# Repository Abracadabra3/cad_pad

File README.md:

# CAD Pad
**A macropad with Autodesk Fusion shortcuts, a numberpad, and general shortcuts.**

## Features
- Layer 0: A numberpad
- Layer 1: Shortcuts for Autodesk Fusion
- Layer 2: General shortcuts for outside of Fusion
- Layer 3: Shorcuts for inside a Fusion sketch
- A shortcut for opening the parameter dialogue
- A made-from-scratch 7-segment display!

## BOM
- 1 unsoldered Seeed XIAO RP2040
- 12 through-hole 1N4148 diodes
- 12 MX-Style switches
- 12 DSA keycaps
- 7 SK6812 MINI-E LEDs
- 4 M3x16mm screws
- 4 M3x5x4mm heatset inserts
- 2 7 pin headers
- 0.91 inch OLED display (Optional)
- 4 pin header (Only if OLED display used)
- EC11 Rotary encoders (Optional)

## Design decisions
I chose the 12 key layout of the CAD Pad to mimic a numberpad and still have extra pins on the Seeeduino. The PCB has a connector for both a rotary encode and an OLED display. Neither are in the firmware right now and there is only enough pins for one at a time, but both are options for the future.
I didn't feel like figuring out how to use the OLED display, so instead I made a 7-segment display with LEDs and coded it to display the layer number!

## References
I followed many tutorials other than the [Stardance guide](https://hackpad.hackclub.com/guide) to making a macropad.
- [Creating a matrix in KiCad](youtube.com/watch?v=8WXpGTIbxlQ)
- [Setting up QMK](youtube.com/watch?v=hjml-K-pV4E)
- [Layers in QMK](keebsforall.com/blogs/mechanical-keyboards-101/how-to-add-layers-in-qmk)
- [Macros in QMK](getreuer.info/posts/keyboards/macros/index.html#simple-macros)

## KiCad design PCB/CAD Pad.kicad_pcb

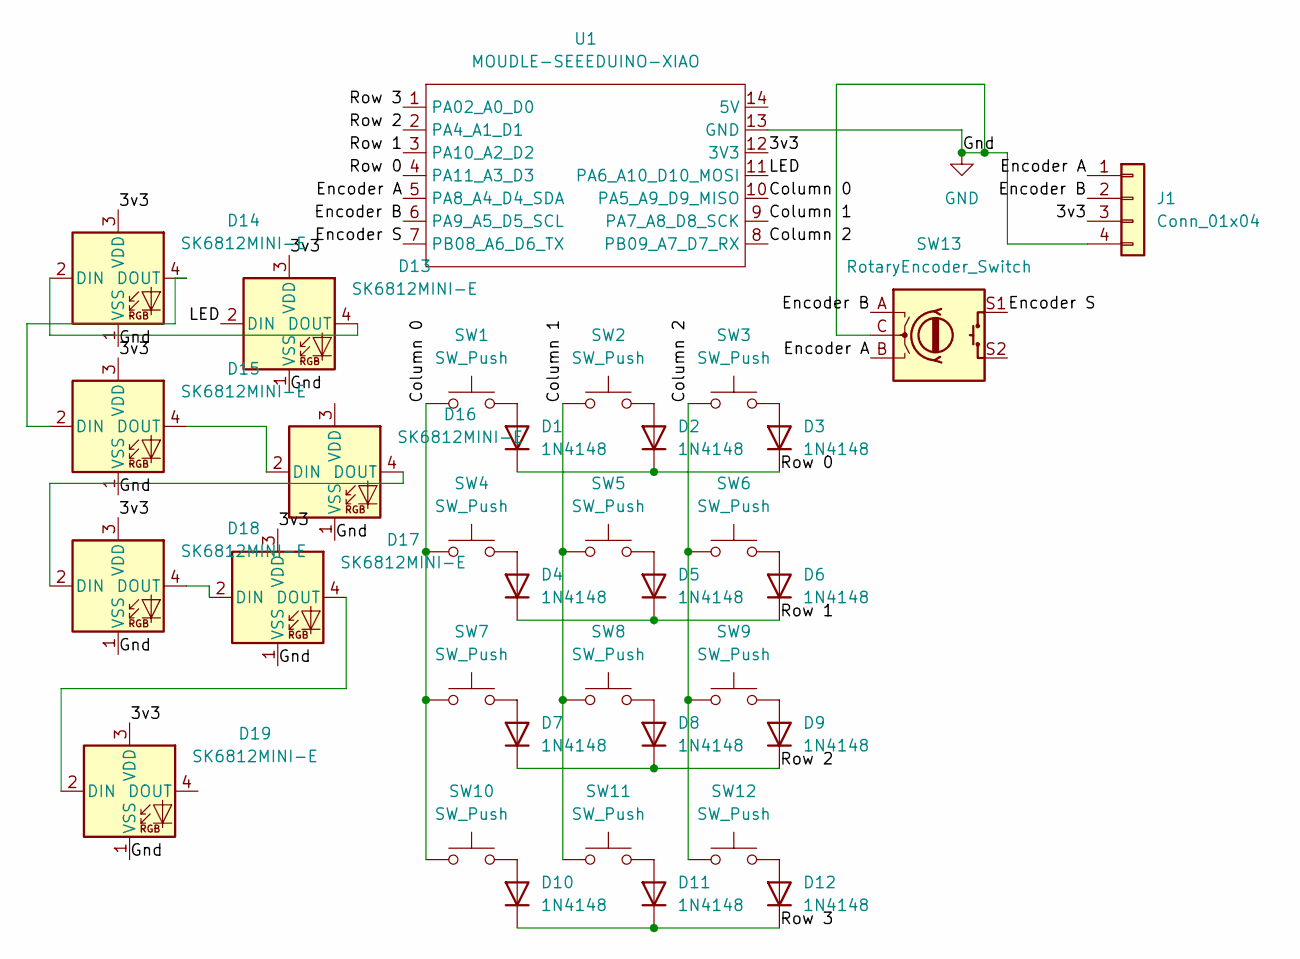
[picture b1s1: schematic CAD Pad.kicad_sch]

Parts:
D1, D2, D3, D4, D5, D6, D7, D8, D9, D10, D11, D12: 1N4148; D_DO-35_SOD27_P7.62mm_Horizontal
D13, D14, D15, D16, D17, D18, D19: SK6812MINI-E; LED_SK6812MINI-E_3.2x2.8mm_P1.5mm_ReverseMount
J1: Conn_01x04; PinSocket_1x04_P2.54mm_Vertical
SW1, SW2, SW3, SW4, SW5, SW6, SW7, SW8, SW9, SW10, SW11, SW12: SW_Push; SW_Cherry_MX_1.00u_PCB
SW13: RotaryEncoder_Switch; RotaryEncoder_Alps_EC11E-Switch_Vertical_H20mm
U1: MOUDLE-SEEEDUINO-XIAO; XIAO-Generic-Hybrid-14P-2.54-21X17.8MM

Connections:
/3v3: D13.3 (VDD), D14.3 (VDD), D15.3 (VDD), D17.3 (VDD), D18.3 (VDD), D19.3 (VDD), J1.3, U1.12 (3V3)
/Column 0: SW1.1, SW4.1, SW7.1, SW10.1, U1.10 (PA5_A9_D9_MISO)
/Column 1: SW2.1, SW5.1, SW8.1, SW11.1, U1.9 (PA7_A8_D8_SCK)
/Column 2: SW3.1, SW6.1, SW9.1, SW12.1, U1.8 (PB09_A7_D7_RX)
/Encoder A: J1.1, SW13.B, U1.5 (PA8_A4_D4_SDA)
/Encoder B: J1.2, SW13.A, U1.6 (PA9_A5_D5_SCL)
/Encoder S: SW13.S1, U1.7 (PB08_A6_D6_TX)
/LED: D13.2 (DIN), U1.11 (PA6_A10_D10_MOSI)
/Row 0: D1.1 (K), D2.1 (K), D3.1 (K), U1.4 (PA11_A3_D3)
/Row 1: D4.1 (K), D5.1 (K), D6.1 (K), U1.3 (PA10_A2_D2)
/Row 2: D7.1 (K), D8.1 (K), D9.1 (K), U1.2 (PA4_A1_D1)
/Row 3: D10.1 (K), D11.1 (K), D12.1 (K), U1.1 (PA02_A0_D0)
GND: D13.1 (VSS), D14.1 (VSS), D15.1 (VSS), D16.1 (VSS), D17.1 (VSS), D18.1 (VSS), D19.1 (VSS), J1.4, SW13.C, U1.13 (GND)
unnamed: D1.2 (A), SW1.2
unnamed: D2.2 (A), SW2.2
unnamed: D3.2 (A), SW3.2
unnamed: D4.2 (A), SW4.2
unnamed: D5.2 (A), SW5.2
unnamed: D6.2 (A), SW6.2
unnamed: D7.2 (A), SW7.2
unnamed: D8.2 (A), SW8.2
unnamed: D9.2 (A), SW9.2
unnamed: D10.2 (A), SW10.2
unnamed: D11.2 (A), SW11.2
unnamed: D12.2 (A), SW12.2
unnamed: D13.4 (DOUT), D14.2 (DIN)
unnamed: D14.4 (DOUT), D15.2 (DIN)
unnamed: D15.4 (DOUT), D16.2 (DIN)
unnamed: D16.4 (DOUT), D18.2 (DIN)
unnamed: D17.2 (DIN), D18.4 (DOUT)
unnamed: D17.4 (DOUT), D19.2 (DIN)

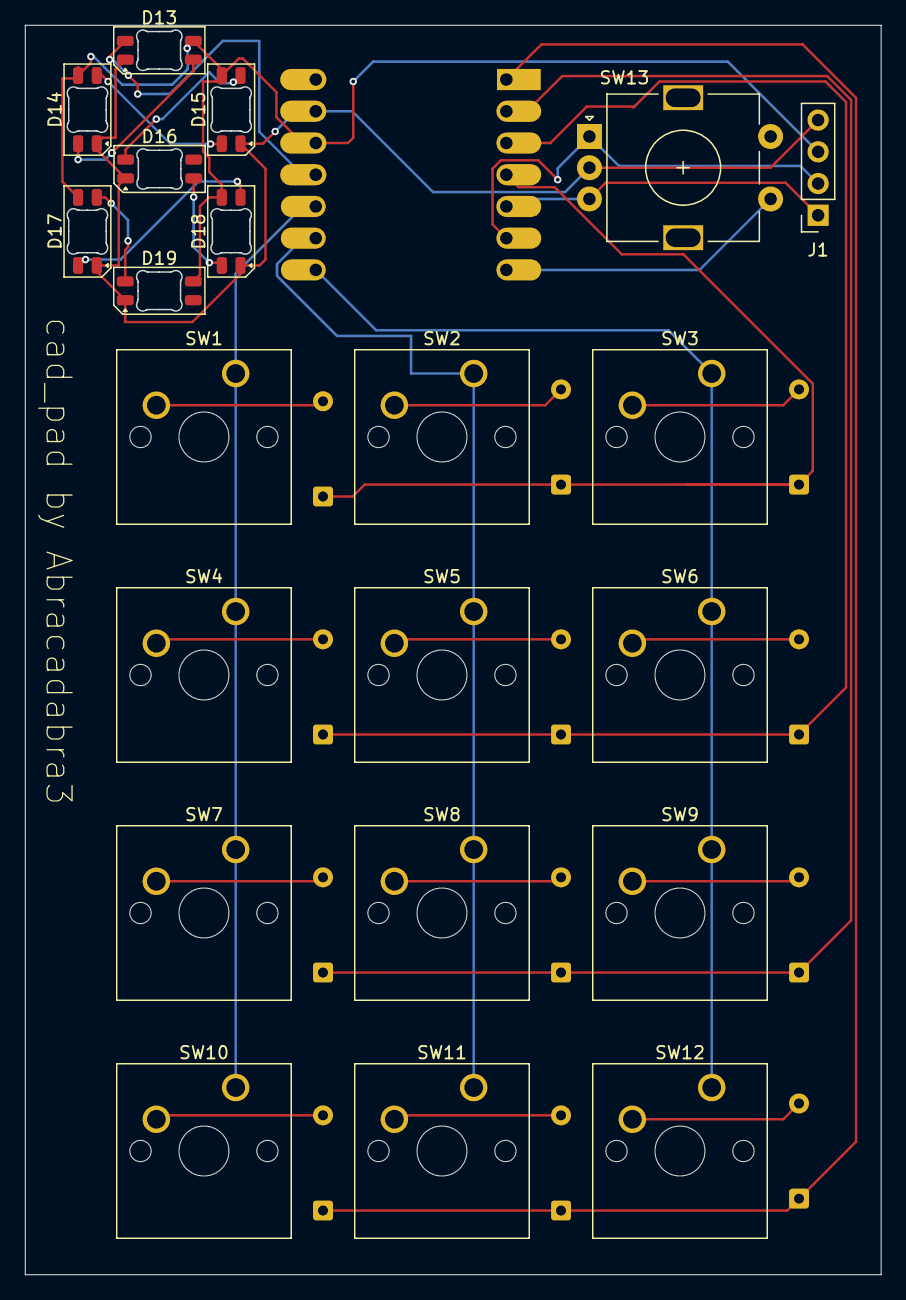
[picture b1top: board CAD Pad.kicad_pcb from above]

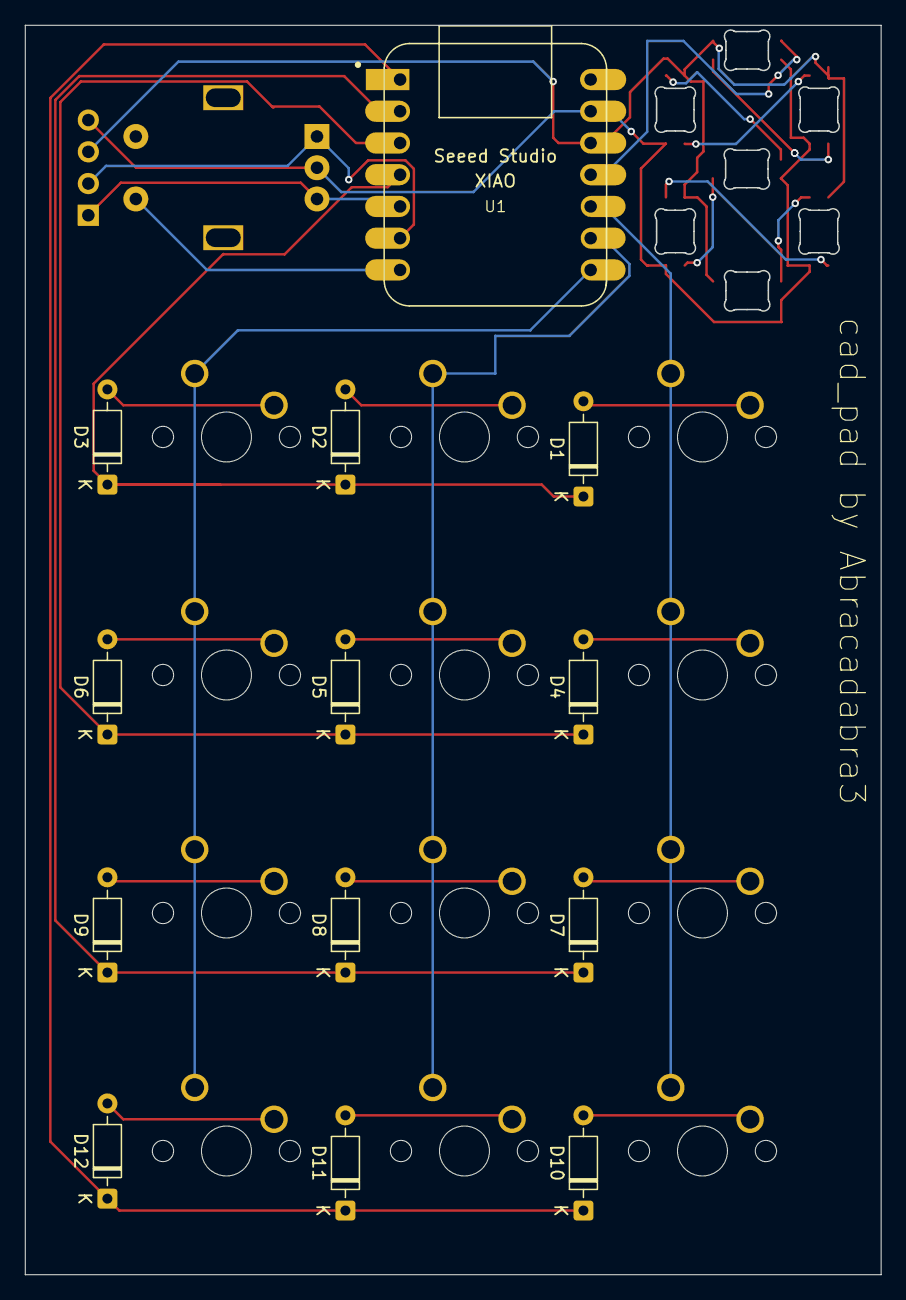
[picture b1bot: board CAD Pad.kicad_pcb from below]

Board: 2 copper layers, 68.4 x 99.9 mm, 34 parts (13 on the bottom side), 31 nets.

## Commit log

2026-06-28 Add all project files
2026-06-28 Add Git username to parts
2026-06-28 Clarify layers in Features section
2026-06-30 Edit BOM
2026-06-30 Add bom.csv
